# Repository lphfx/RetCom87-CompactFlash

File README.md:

# RetCom87-CompactFlash
CompactFlash Expansion Board for RetCom87 (Retrofuturistic Hardware VIP @ Georgia Tech)

(Currently in incomplete state)

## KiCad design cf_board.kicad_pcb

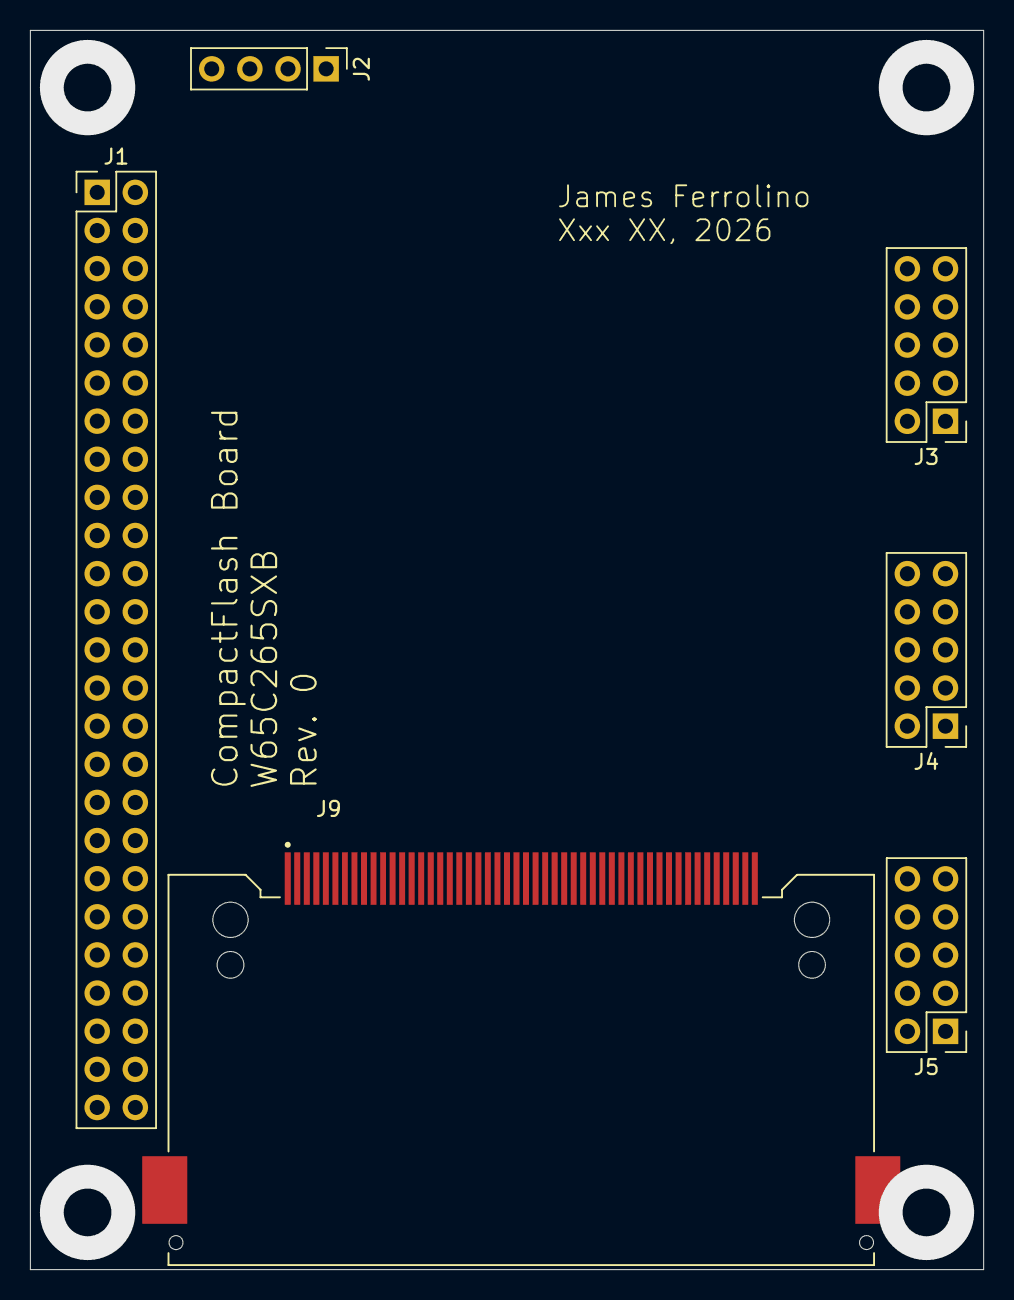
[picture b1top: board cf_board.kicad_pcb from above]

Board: 2 copper layers, 63.5 x 82.6 mm, 6 parts (0 on the bottom side), 2 nets.

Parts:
J1: XBus265; PinHeader_2x25_P2.54mm_Vertical
J2: TGx; PinHeader_1x04_P2.54mm_Vertical
J3: P4x; PinHeader_2x05_P2.54mm_Vertical
J4: P5x; PinHeader_2x05_P2.54mm_Vertical
J5: P6x; PinHeader_2x05_P2.54mm_Vertical
J9: N7E50-Q516RB-40 (CF Slot); 3M_N7E50-Q516RB-40

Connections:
GND: J9.1, J9.50
VCC: J9.13, J9.38
